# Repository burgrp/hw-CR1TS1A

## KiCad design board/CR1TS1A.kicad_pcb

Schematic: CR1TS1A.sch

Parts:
D2: LED; LED_0805
D3: BAT54C; SOT-23
IN1: CONN_01X03; HB-9500-3P
K1: RELAY_2; RT314_Relay
OUT1: CONN_01X03; HB-9500-3P
Q1: MMBT3904; SOT-23
R1: 1k5; R_0805
R2: 270R; R_0805
R12: 4k7; R_0805
TS1: Conn_01x03; HB-9500-3P

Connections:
/5V: D3.3, K1.1; also elsewhere on the board
/ESP/GPIO12: R12.1, TS1.2; also elsewhere on the board
/LED: R2.1; also elsewhere on the board
/MAINS-E: IN1.1, OUT1.1
/MAINS-L-I: IN1.3, K1.11, K1.21; also elsewhere on the board
/MAINS-L-O: K1.14, K1.24, OUT1.3
/MAINS-N: IN1.2, OUT1.2; also elsewhere on the board
/SW: R1.2; also elsewhere on the board
GND: D2.1, Q1.2 (E), TS1.1; also elsewhere on the board
unnamed: D2.2, R2.2
unnamed: D3.2, K1.2, Q1.3 (C)
unnamed: Q1.1 (B), R1.1
VCC: R12.2, TS1.3; also elsewhere on the board

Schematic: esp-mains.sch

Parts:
C1: 1u; C_0805
C2: 22n; C_0805
C3: 47u; C_0805
C4, C7: 100n; C_0805
C5, C6: 22p; C_0805
D1: BAT54C; SOT-23
L1: Ferrite bead; R_0805
P1: USB_OTG; conn_usb_B_micro_smd-2
Q2, Q3: MMBT3904; SOT-23
R3, R4: 1k5; R_0805
R5, R6, R7, R8, R9, R10, R11: 10k; R_0805
U1: RT9193; SOT-23-5
U2: HLK-PM01
U4: ESP-12
U5: CH340G; SO-16-N
X1: 12MHz; Crystal_SMD_SeikoEpson_TSX3225-4pin_3.2x2.5mm

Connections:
/5V: C1.1, D1.3, U1.1, U1.3; also elsewhere on the board
/ESP/5V-MAINS: D1.2, U2.4
/ESP/5V-USB: D1.1, P1.1
/ESP/ADC: U4.2
/ESP/D+: P1.3, U5.5
/ESP/D-: P1.2, U5.6
/ESP/DTR: Q3.2 (E), R10.1, U5.13
/ESP/EN: R7.1, U4.3
/ESP/GPIO0: Q3.3 (C), R5.1, U4.12
/ESP/GPIO2: R6.1, U4.11
/ESP/GPIO12: U4.6; also elsewhere on the board
/ESP/GPIO13: U4.7
/ESP/GPIO14: U4.5
/ESP/GPIO15: R9.1, U4.10
/ESP/GPIO16: U4.4
/ESP/RESET: C7.2, Q2.3 (C), R8.1, U4.1
/ESP/RTS: Q2.2 (E), R11.2, U5.14
/ESP/RX: R3.1, U4.15
/ESP/TX: R4.1, U4.16
/LED: U4.14; also elsewhere on the board
/MAINS-L-I: U2.2; also elsewhere on the board
/MAINS-N: U2.1; also elsewhere on the board
/SW: U4.13; also elsewhere on the board
GND: C1.2, C2.2, C3.2, C4.2, C5.2, C6.2, C7.1, P1.5, P1.6, R9.2, U1.2, U2.3, U4.9, U5.1, X1.2, X1.4; also elsewhere on the board
unnamed: C2.1, U1.4
unnamed: C3.1, L1.2, U1.5
unnamed: C5.1, U5.7, X1.1
unnamed: C6.1, U5.8, X1.3
unnamed: Q2.1 (B), R10.2
unnamed: Q3.1 (B), R11.1
unnamed: R3.2, U5.2
unnamed: R4.2, U5.3
VCC: C4.1, L1.1, R5.2, R6.2, R7.2, R8.2, U4.8, U5.4, U5.16; also elsewhere on the board

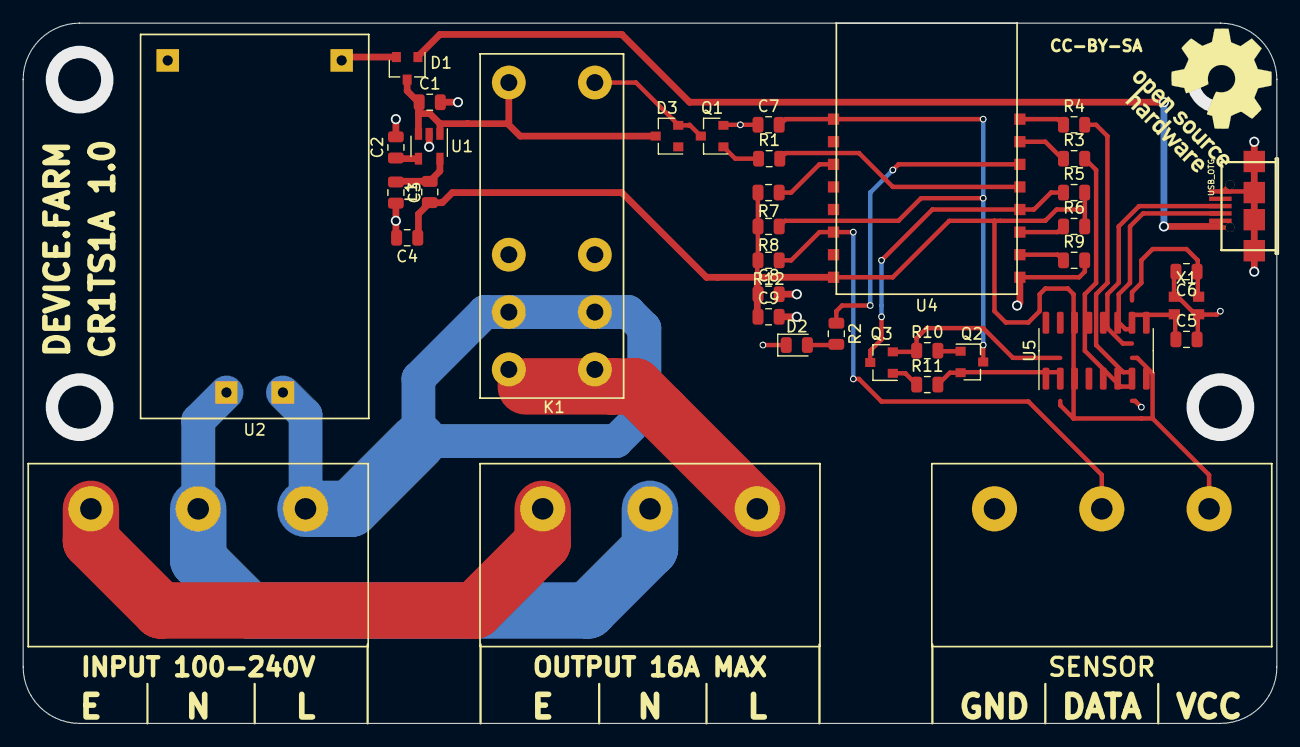
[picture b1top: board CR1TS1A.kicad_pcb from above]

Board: 2 copper layers, 111.0 x 62.0 mm, 38 parts (0 on the bottom side), 34 nets.

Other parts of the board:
C8, C9: 47u; C_0805_2012Metric

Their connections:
GND: C8.2, C9.2; also elsewhere on the board
VCC: C8.1, C9.1; also elsewhere on the board

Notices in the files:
board/CR1TS1A.kicad_pcb:
CC-BY-SA
